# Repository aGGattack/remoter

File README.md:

# Bachelor Project - Wireless Remote Controller System

Remote control system for a robot, built around an **Adafruit Feather M0** with an **RFM69 433 MHz** radio, consisting of a handheld remote controller and a robot-side receiver.

---

## Repository Structure

```
bachelor/
├── remoter/                         # Firmware source code
│   ├── Remote/                      # Handheld remote controller
│   │   ├── src/main.cpp             # Main loop, 10Hz control rate
│   │   ├── src/RadioTrans.cpp       # RFM69 radio (TX, ACK)
│   │   ├── src/Joystick.cpp         # Analog joystick driver
│   │   ├── src/OledDis.cpp          # SSD1306 OLED display driver
│   │   ├── include/                 # Headers
│   │   └── platformio.ini           # PlatformIO config
│   │
│   └── RobotSide/                   # Robot-mounted receiver
│       ├── src/main.cpp             # Main loop, serial bridge
│       ├── src/RemoteTransiver.cpp  # RFM69 radio (RX, ACK) + serial
│       ├── include/                 # Headers
│       └── platformio.ini           # PlatformIO config
│
├── UniRemote/                       # Remote controller PCB (KiCad)
│   ├── PCB remote.kicad_sch         # Schematic
│   ├── PCB remote.kicad_pcb         # PCB layout
│   ├── PCB remote.kicad_pro         # Project file
│   └── Remote-footprints.pretty/    # Custom footprints
│
├── UniRobot/                        # Robot receiver PCB (KiCad)
│   ├── UniRobot.kicad_sch           # Schematic
│   ├── UniRobot.kicad_pcb           # PCB layout
│   ├── UniRobot.kicad_pro           # Project file
│   └── Remote-footprints.pretty/    # Custom footprints
│
├── Project tests/                   # RFM69 performance characterization
│   ├── BitRateLatencyTest.py        # Latency vs bitrate (1.2-250 kbps)
│   ├── PackageSizeLatencyTest.py    # Latency vs packet size (5-64 B)
│   ├── MaxDistance/                 # Packet loss vs distance
│   ├── RSSI_Antenna_test/           # RSSI vs distance + antenna length
│   ├── OrrientationTest/            # RSSI vs antenna orientation
│   └── latency_Bitrate_test/        # Plotting scripts
│
├── project_plan/                    # Project plan (LaTeX, diagrams)
├── Bachelor_Contract.pdf
├── appendix_code_listings.tex       # Full source listings for report
├── UniRemote v1.zip, v1.5.zip, ...  # PCB version archives
└── UniRobot v1.zip, v1.5.zip, ...
```

---

## Hardware

| Component | Description |
|-----------|-------------|
| **MCU** | Adafruit Feather M0 (ATSAMD21G18A, ARM Cortex-M0+) |
| **Radio** | RFM69HCW 433 MHz transceiver |
| **Display** | SSD1306 128x32 OLED, I2C |
| **Input** | Analog dual-axis joystick + push button (E-stop) |
| **Battery** | LiPo with voltage monitor via A7 |

---

## Firmware

### How It Works

- **Remote** reads joystick X/Y (8-bit), button state, and battery voltage. Transmits 3-byte packets every 100 ms to the robot (NodeID=1). Receives ACK containing robot battery voltage and robot name. Displays RSSI, local & remote battery, and robot name on the OLED.
- **RobotSide** receives joystick packets and forwards them over serial to a Raspberry Pi as `x:<val>, y:<val>, btn:<val>`. Sends ACKs with robot battery and name (parsed from Pi serial input `name:<n>,bat:<v>`). Drives an E-stop output pin.

### Prerequisites

- [PlatformIO](https://platformio.org/)

### Build & Upload

```bash
# Remote controller
cd remoter/Remote
pio run -e adafruit_feather_m0 --target upload

# Robot-side receiver
cd remoter/RobotSide
pio run -e adafruit_feather_m0 --target upload
```

### Serial Monitor

```bash
pio device monitor --baud 115200
```

---

## PCB Design

Both PCBs designed in **KiCad**. To open:

```
# Remote
UniRemote/PCB remote.kicad_pro

# Robot
UniRobot/UniRobot.kicad_pro
```

---

## RF Performance Tests

Python scripts in `Project tests/` characterize the RFM69 link:

| Test | What it measures |
|------|-----------------|
| `BitRateLatencyTest.py` | One-way latency from 1.2 to 250 kbps |
| `PackageSizeLatencyTest.py` | Latency vs payload size at multiple bitrates |
| `MaxDistance/packagelossTest.py` | Packet loss ratio from 20 to 70 m |
| `RSSI_Antenna_test/RSSItest.py` | RSSI vs distance for a given antenna |
| `OrrientationTest/OrrientationsTest.py` | RSSI vs antenna orientation |
| Various `plot_*.py` | Generate plots from collected CSV data |

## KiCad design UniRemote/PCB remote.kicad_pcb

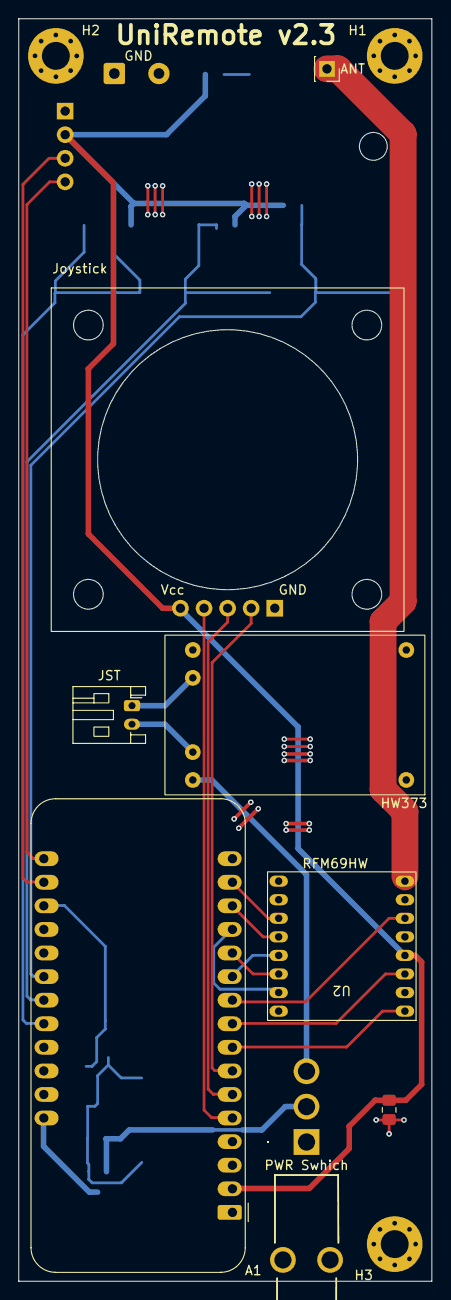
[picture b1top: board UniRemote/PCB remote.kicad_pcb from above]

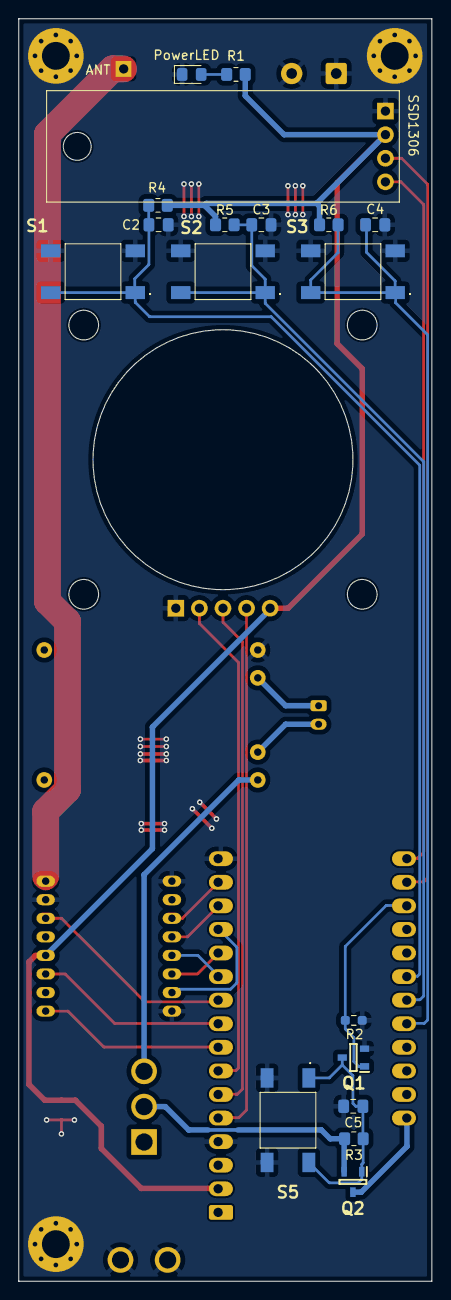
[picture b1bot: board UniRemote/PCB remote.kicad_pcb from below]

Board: 2 copper layers, 44.5 x 136.0 mm, 30 parts (18 on the bottom side), 27 nets.

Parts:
A1: Adafruit_Feather_M0_Adalogger; Adafruit_Feather
ANT: Conn_01x01; PinSocket_1x01_P2.54mm_Vertical
C1, C5: 10uF; C_0805_2012Metric_Pad1.18x1.45mm_HandSolder
C2, C3, C4: 100nF; C_0805_2012Metric_Pad1.18x1.45mm_HandSolder
D1: LED; LED_0805_2012Metric_Pad1.15x1.40mm_HandSolder
GND: Conn_01x02_Socket; SolderWire-0.5sqmm_1x02_P4.8mm_D0.9mm_OD2.3mm
H1, H2, H3: MountingHole_Pad; MountingHole_3mm_Pad_Via
HW373: HW373
JST: 02_Socket; JST_PH_S2B-PH-K_1x02_P2.00mm_Horizontal
PWR Swhich: 100SP1T1B1M7QEH; 100SP1T1B1M7QEH(redSwitch)
Q1: BSS138; nmos
Q2: PMV28XPEAR; Pmos
R1: 280; R_0805_2012Metric_Pad1.20x1.40mm_HandSolder
R2: 47k; R_0603_1608Metric_Pad0.98x0.95mm_HandSolder
R3: 220k; R_0805_2012Metric_Pad1.20x1.40mm_HandSolder
R4, R5, R6: 10k; R_0805_2012Metric_Pad1.20x1.40mm_HandSolder
S1, S2, S3, S5: TL3301TF160QG
SSD1306: SSD1306; SSD1306(128x32)
U2: RFM69HW; RFM69HCW(homemade)
U3: Joystick

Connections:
+3.3V: A1.2 (3V3), C1.2, R1.1, R4.1, R5.1, R6.1, SSD1306.2 (VCC), U2.4 (3.3V), U3.5 (VCC)
+BATT: A1.28 (VBAT), Q2.3 (D)
/B-D10-S1: A1.22 (D10), C2.1, R4.2, S1.1 (COM_1), S1.2 (COM_2)
/B-D11-S2: A1.23 (D11), C3.1, R5.2, S2.1 (COM_1), S2.2 (COM_2)
/B-D12-S3: A1.24 (D12), C4.1, R6.2, S3.1 (COM_1), S3.2 (COM_2)
/J-A0-Sel: A1.7 (A2), U3.2 (Sel)
/J-A1-Yout: A1.6 (A1), U3.3 (Yout)
/J-A2-Xout: A1.5 (DAC0/A0), U3.4 (Xout)
/P-S4-BAT: PWR Swhich.2 (COM), Q2.2 (S), R3.1
/P-USBC-S4: HW373.3 (out+), PWR Swhich.3 (NO)
/R-A3-D02: A1.8 (A3), U2.1 (DIO2)
/R-A4-DO0: A1.9 (A4), U2.3 (DIO0)
/R-A5-DO3: A1.10 (A5), U2.6 (DIO3)
/R-D0-NSS: A1.14 (RX/D0), U2.12 (NSS)
/R-D1-RT: A1.15 (TX/D1), U2.11 (RESET)
/R-D22-MISO: A1.13 (MISO/D22), U2.15 (MISO)
/R-D23-MOSI: A1.12 (MOSI/D23), U2.14 (MOSI)
/R-D24-SCK: A1.11 (SCK/D24), U2.13 (SCK)
/SCL: A1.18 (SCL/D21), SSD1306.3 (SCK)
/SDA: A1.17 (SDA/D20), SSD1306.4 (SDA)
GND: A1.4 (GND), A1.16 (GND), C1.1, C2.2, C3.2, C4.2, C5.2, D1.1 (K), GND.1, GND.2, H1.1, H2.1, H3.1, HW373.4 (out-), PWR Swhich.4 (MH1), PWR Swhich.5 (MH2), Q1.2 (S), R2.2, S1.3 (NO_1), S1.4 (NO_2), S2.3 (NO_1), S2.4 (NO_2), S3.3 (NO_1), S3.4 (NO_2), S5.3 (NO_1), S5.4 (NO_2), SSD1306.1 (GND), U2.7 (GND), U2.9 (GND), U2.16 (GND), U3.1 (GND)
unnamed: D1.2 (A), R1.2
unnamed: ANT.1, U2.8 (ANA)
unnamed: HW373.2 (b-), JST.1
unnamed: HW373.1 (b+), JST.2
unnamed: C5.1, Q1.3 (D), Q2.1 (G), R3.2, S5.1 (COM_1), S5.2 (COM_2)
PWRC: A1.19 (D5), Q1.1 (G), R2.1

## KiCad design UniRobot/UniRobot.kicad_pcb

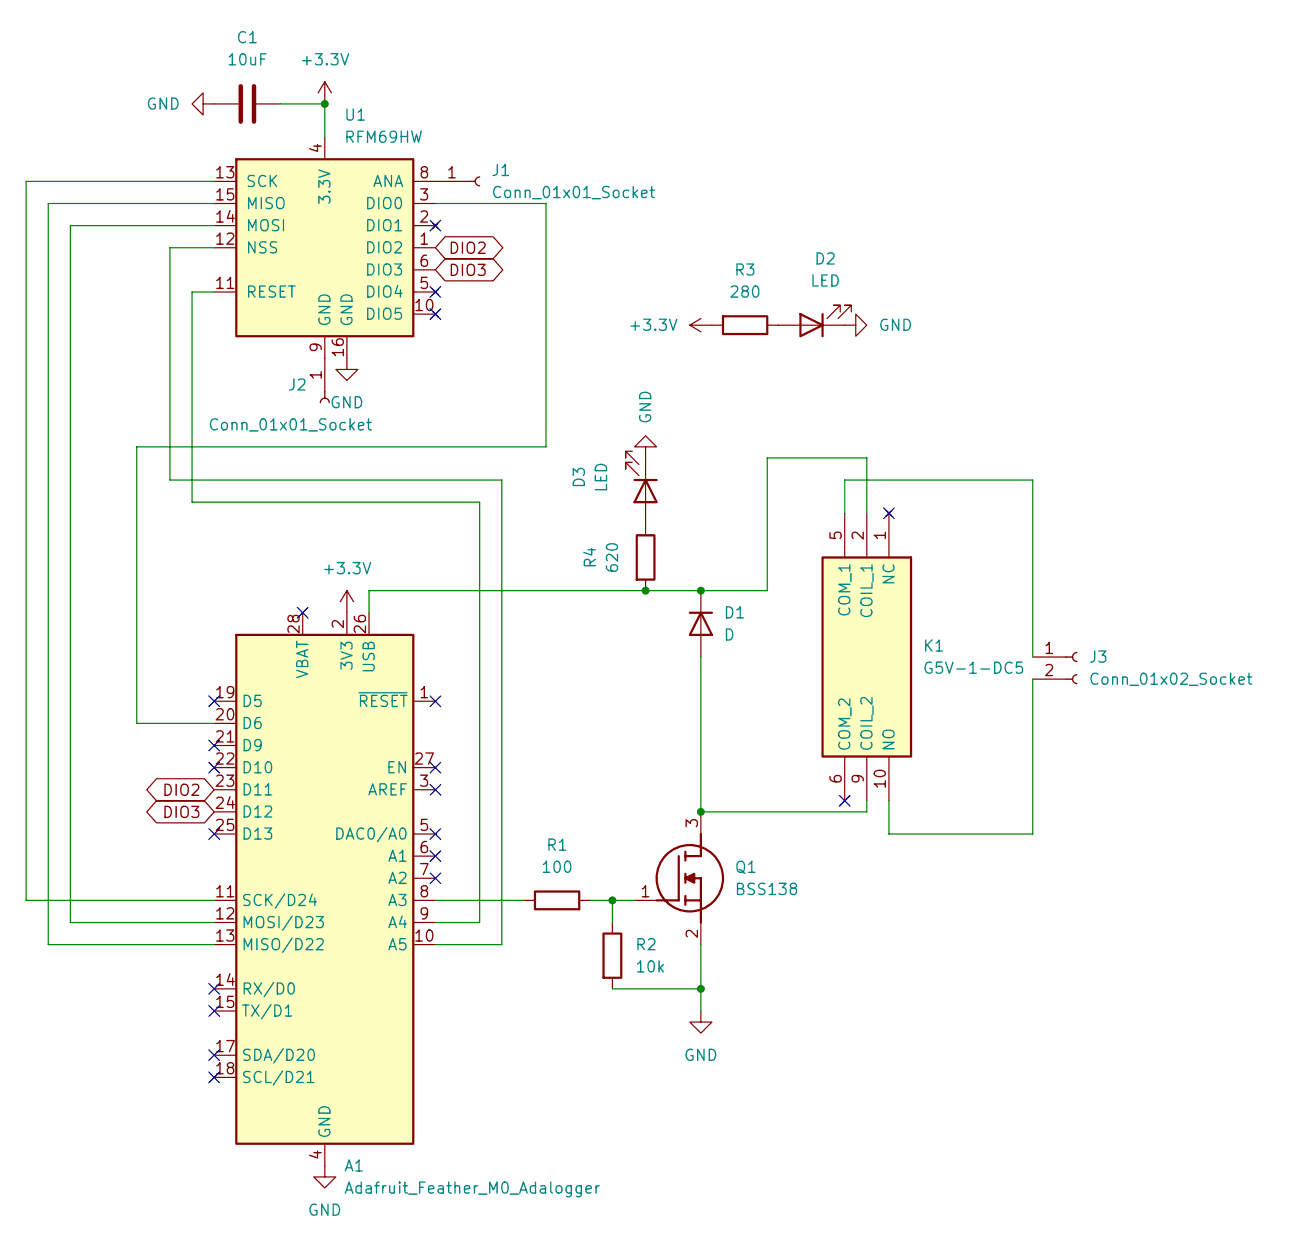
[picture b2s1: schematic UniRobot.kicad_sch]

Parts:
A1: Adafruit_Feather_M0_Adalogger; Adafruit_Feather
C1: 10uF; C_0805_2012Metric_Pad1.18x1.45mm_HandSolder
D1: D; SODFL3816X120N(diode den vi har)
D2, D3: LED; LED_0805_2012Metric_Pad1.15x1.40mm_HandSolder
J1, J2: Conn_01x01_Socket; PinSocket_1x01_P2.54mm_Vertical
J3: Conn_01x02_Socket; PinSocket_1x02_P2.54mm_Vertical
K1: G5V-1-DC5; G5V1DC24; Mouser Part Number 653-G5V-1-DC5
Q1: BSS138; nmos; Mouser Part Number 512-BSS138
R1: 100; R_0805_2012Metric_Pad1.20x1.40mm_HandSolder
R2: 10k; R_0805_2012Metric_Pad1.20x1.40mm_HandSolder
R3: 280; R_0805_2012Metric_Pad1.20x1.40mm_HandSolder
R4: 620; R_0805_2012Metric_Pad1.20x1.40mm_HandSolder
U1: RFM69HW; RFM69HCW(homemade)

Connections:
+3.3V: A1.2 (3V3), C1.2, R3.2, U1.4 (3.3V)
DIO2: A1.23 (D11), U1.1 (DIO2)
DIO3: A1.24 (D12), U1.6 (DIO3)
GND: A1.4 (GND), A1.16 (GND), C1.1, D2.1 (K), D3.1 (K), Q1.2 (S), R2.2, U1.16 (GND)
unnamed: A1.8 (A3), R1.1
unnamed: A1.9 (A4), U1.11 (RESET)
unnamed: A1.10 (A5), U1.12 (NSS)
unnamed: A1.20 (D6), U1.3 (DIO0)
unnamed: A1.13 (MISO/D22), U1.15 (MISO)
unnamed: A1.12 (MOSI/D23), U1.14 (MOSI)
unnamed: A1.11 (SCK/D24), U1.13 (SCK)
unnamed: A1.26 (USB), D1.1 (K), K1.2 (COIL_1), R4.2
unnamed: D1.2 (A), K1.9 (COIL_2), Q1.3 (D)
unnamed: D2.2 (A), R3.1
unnamed: D3.2 (A), R4.1
unnamed: J1.1, U1.8 (ANA)
unnamed: J2.1, U1.9 (GND)
unnamed: J3.1, K1.5 (COM_1)
unnamed: J3.2, K1.10 (NO)
unnamed: Q1.1 (G), R1.2, R2.1

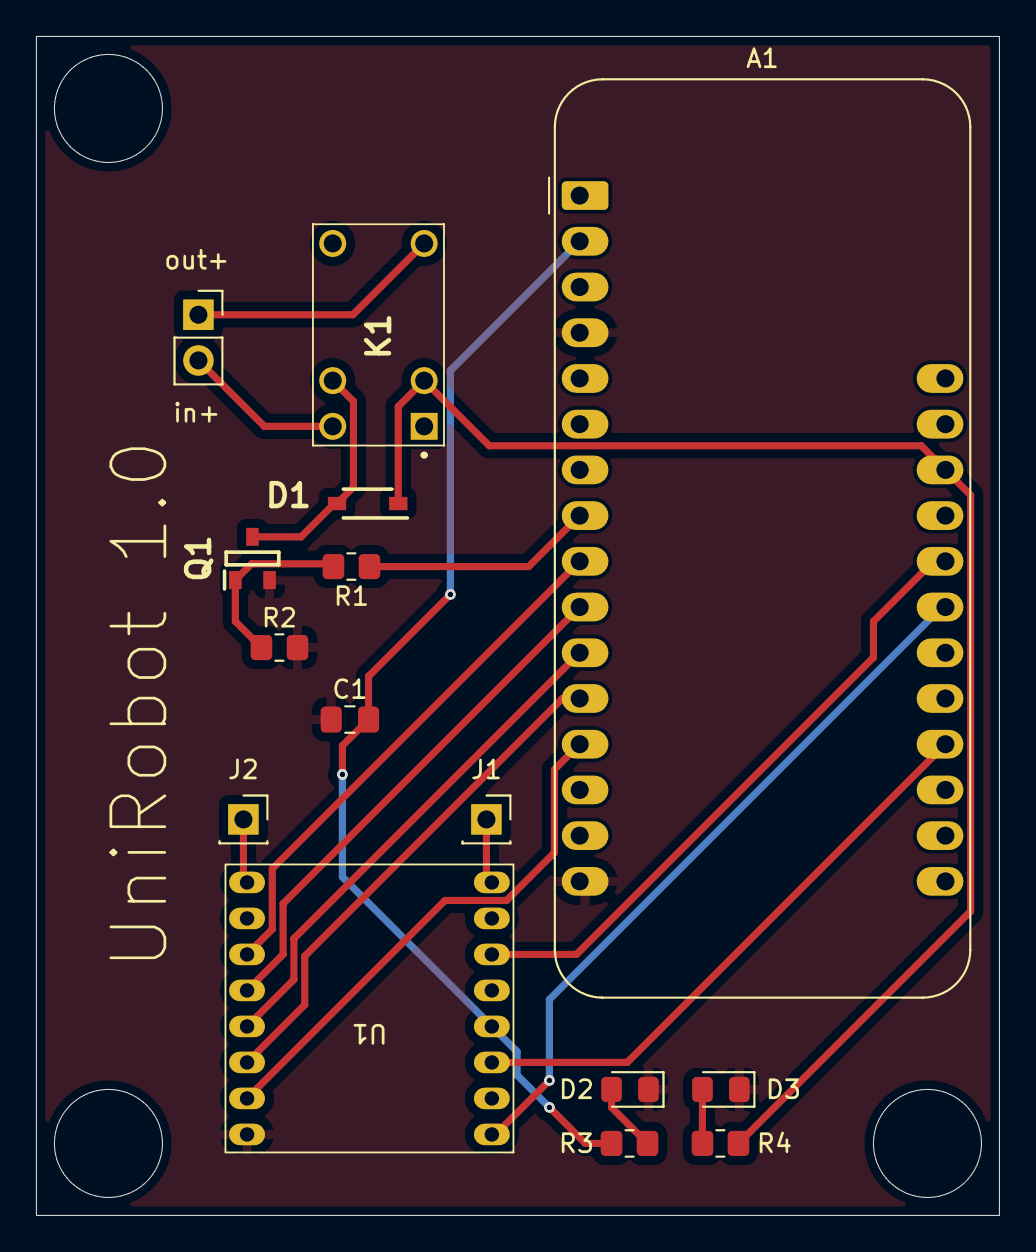
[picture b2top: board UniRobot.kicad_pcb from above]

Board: 2 copper layers, 53.5 x 65.5 mm, 15 parts (0 on the bottom side), 20 nets.

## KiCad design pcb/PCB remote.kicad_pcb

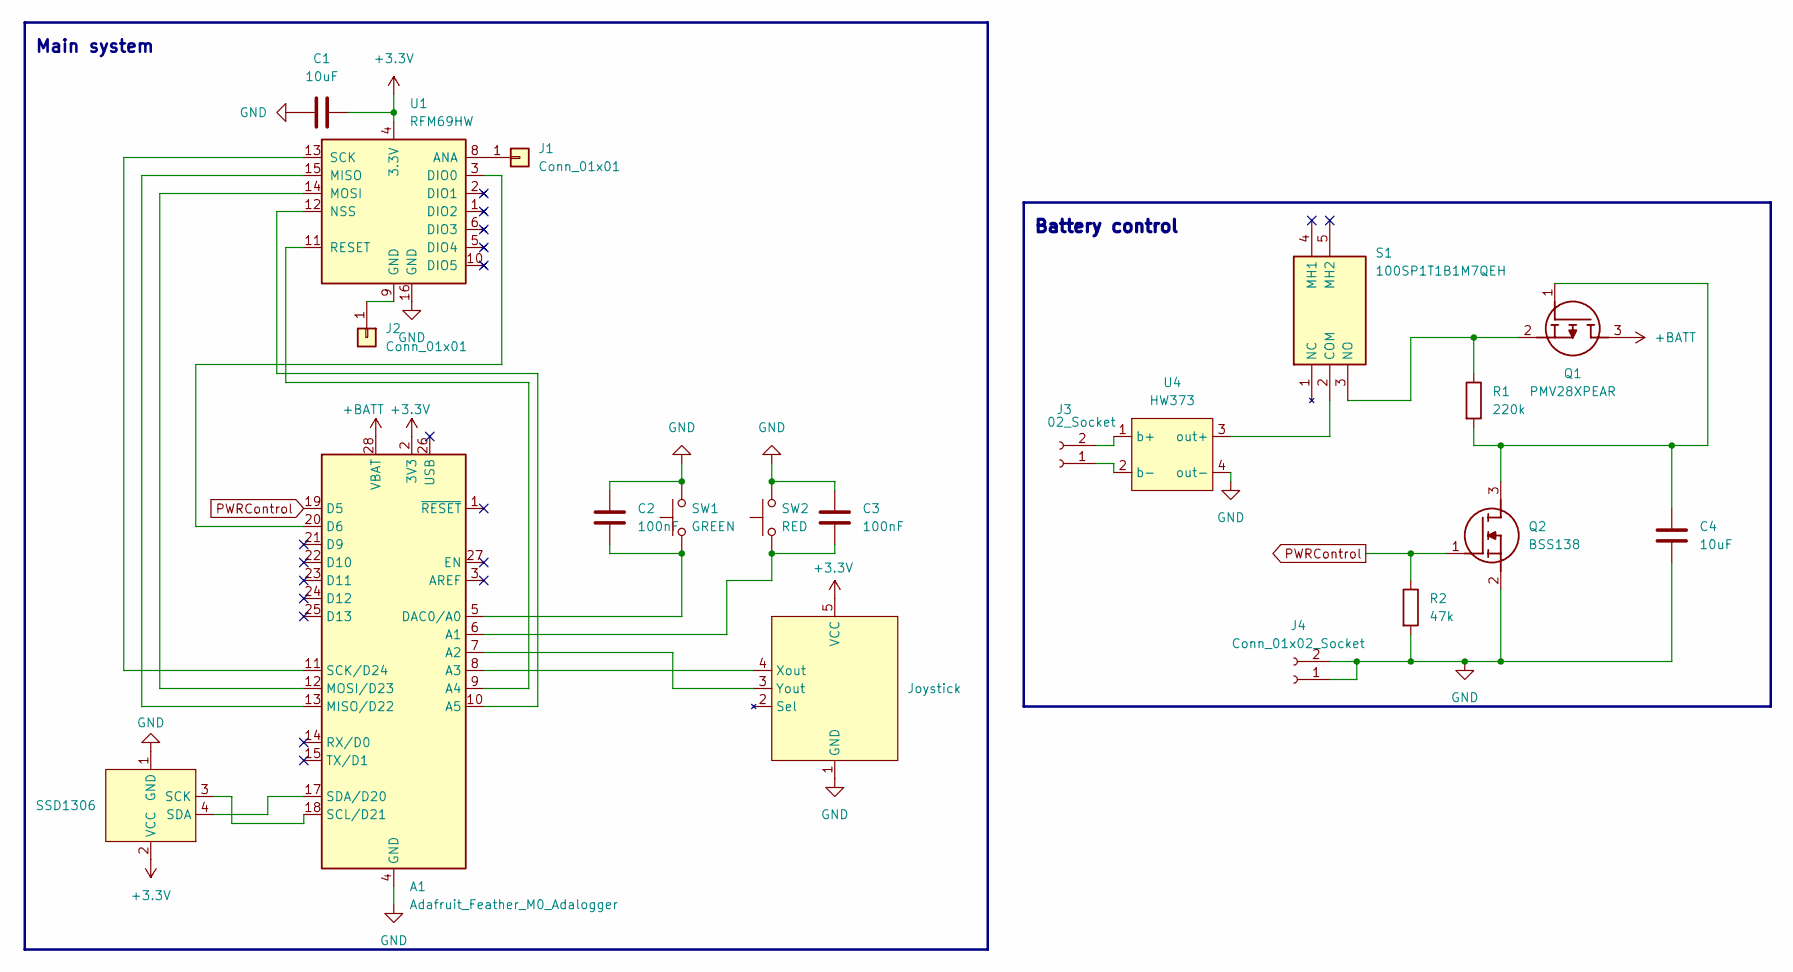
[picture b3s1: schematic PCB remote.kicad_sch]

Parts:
A1: Adafruit_Feather_M0_Adalogger; Adafruit_Feather
C1, C4: 10uF; C_0805_2012Metric_Pad1.18x1.45mm_HandSolder
C2, C3: 100nF; C_0805_2012Metric_Pad1.18x1.45mm_HandSolder
J1, J2: Conn_01x01; PinSocket_1x01_P2.54mm_Vertical
J3: 02_Socket; JST_PH_S2B-PH-K_1x02_P2.00mm_Horizontal
J4: Conn_01x02_Socket; SolderWire-0.5sqmm_1x02_P4.8mm_D0.9mm_OD2.3mm
Q1: PMV28XPEAR; Pmos; Mouser Part Number 771-PMV28XPEAR
Q2: BSS138; nmos; Mouser Part Number 512-BSS138
R1: 220k; R_0805_2012Metric_Pad1.20x1.40mm_HandSolder
R2: 47k; R_0603_1608Metric_Pad0.98x0.95mm_HandSolder
S1: 100SP1T1B1M7QEH; 100SP1T1B1M7QEH(redSwitch); Mouser Part Number 612-100SP1T1B1M7QEH
SW1: GREEN; PinSocket_1x02_P2.54mm_Vertical
SW2: RED; PinSocket_1x02_P2.54mm_Vertical
U1: RFM69HW; RFM69HCW(homemade)
U2: SSD1306; SSD1306(128x32)
U3: Joystick
U4: HW373

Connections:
+3.3V: A1.2 (3V3), C1.2, U1.4 (3.3V), U2.2 (VCC), U3.5 (VCC)
+BATT: A1.28 (VBAT), Q1.3 (D)
GND: A1.4 (GND), A1.16 (GND), C1.1, C2.1, C3.1, C4.2, J4.1, J4.2, Q2.2 (S), R2.2, SW1.2, SW2.2, U1.16 (GND), U2.1 (GND), U3.1 (GND), U4.4 (out-)
unnamed: A1.6 (A1), C3.2, SW2.1
unnamed: A1.7 (A2), U3.3 (Yout)
unnamed: A1.8 (A3), U3.4 (Xout)
unnamed: A1.9 (A4), U1.11 (RESET)
unnamed: A1.10 (A5), U1.12 (NSS)
unnamed: A1.20 (D6), U1.3 (DIO0)
unnamed: A1.5 (DAC0/A0), C2.2, SW1.1
unnamed: A1.13 (MISO/D22), U1.15 (MISO)
unnamed: A1.12 (MOSI/D23), U1.14 (MOSI)
unnamed: A1.11 (SCK/D24), U1.13 (SCK)
unnamed: A1.18 (SCL/D21), U2.3 (SCK)
unnamed: A1.17 (SDA/D20), U2.4 (SDA)
unnamed: J1.1, U1.8 (ANA)
unnamed: J2.1, U1.9 (GND)
unnamed: J3.1, U4.2 (b-)
unnamed: J3.2, U4.1 (b+)
unnamed: C4.1, Q1.1 (G), Q2.3 (D), R1.2
unnamed: Q1.2 (S), R1.1, S1.3 (NO)
unnamed: S1.2 (COM), U4.3 (out+)
PWRControl: A1.19 (D5), Q2.1 (G), R2.1

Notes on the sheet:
Battery control
Main system

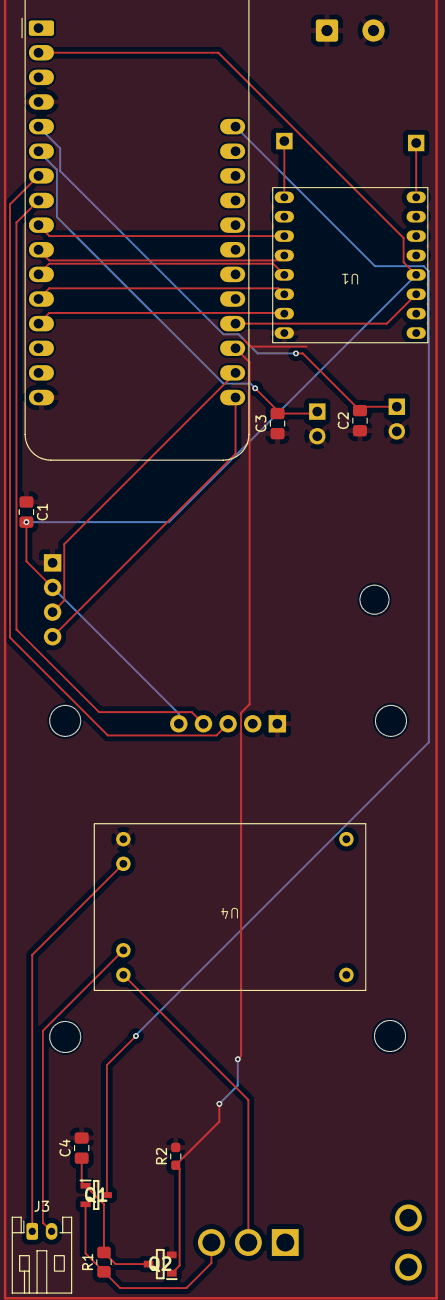
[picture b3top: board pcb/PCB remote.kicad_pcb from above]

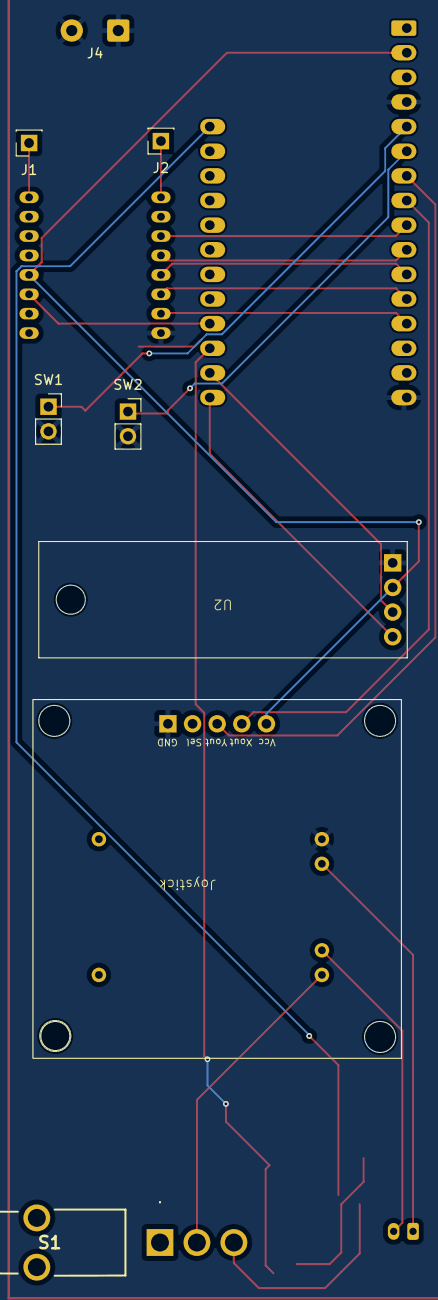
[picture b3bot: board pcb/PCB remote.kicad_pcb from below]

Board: 2 copper layers, 20 parts (8 on the bottom side), 23 nets.

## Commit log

2026-03-04 gitIgnore updated
2026-03-04 Add Robot and join them
2026-03-04 no workspace and readme
2026-03-06 Combined button and joystick for less packages
2026-03-19 Add KiCad PCB files for remote control
2026-03-19 small changes to transivers
2026-03-19 Update PCB design with latest changes
2026-03-19 Restructure repo: move code to remoter/ folder, add pcb/ sibling folder for KiCad files
2026-03-19 readme added
2026-03-19 readme changed
2026-03-24 ny pcb og noget nyt code glete at gemme de andre dage men her er et push
2026-03-25 lavede robot side pcb.
2026-03-30 filerne virkede ikke så tog dem der virkede og smid ind nu virker de og har added batteri måler
2026-03-30 Har lavet begge pcber om. Remote har ændret struktur for mere håndholdt design og ekstra knapper plus LEDer. roboside har fået ny relay og LEDer
2026-04-28 kode virker med robot
2026-05-27 Add test scripts, PCB design files, and appendix code listings
2026-06-07 Update README to reflect actual project structure
